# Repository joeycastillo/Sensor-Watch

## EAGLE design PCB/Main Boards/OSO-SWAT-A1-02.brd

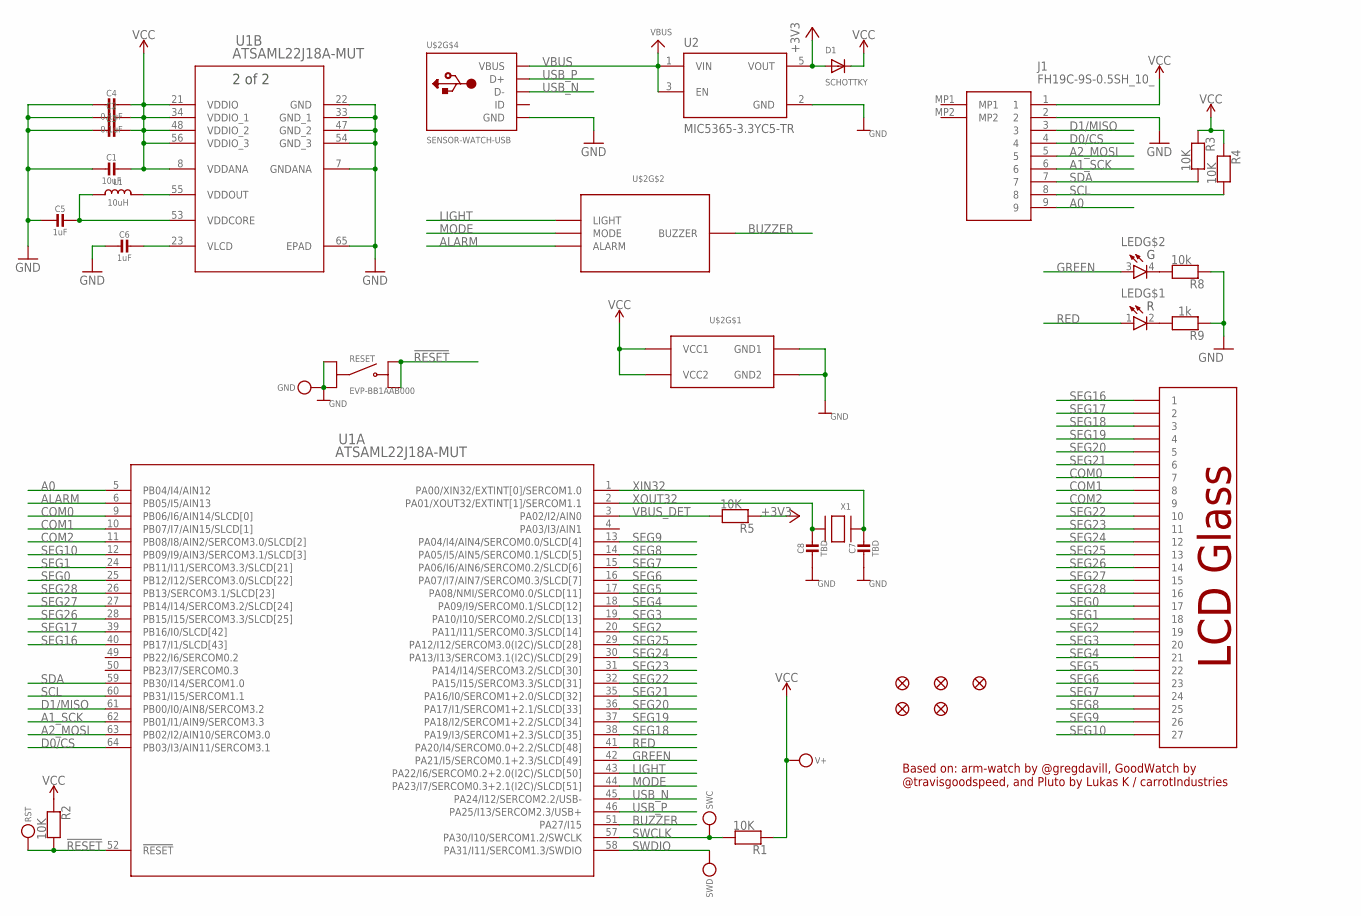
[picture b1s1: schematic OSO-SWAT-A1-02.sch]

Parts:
C1: 10uF; _0603MP
C2, C3, C4: 0.1uF; _0603MP
C5, C6: 1uF; _0603MP
C7, C8: TBD; _0402MP
D1: SCHOTTKY; SOD-323F
FID1, FID2, FID3, FID4, FID6: FIDUCIAL_1MM
GND: MICROBUILDER_TESTPOINTROUND1.5MM; MICROBUILDER_TESTPOINT_ROUND_1.5MM
J1: FH19C-9S-0.5SH_10_; FH19C9S05SH10
L1: 10uH; MICROBUILDER__0805MP
LED: QBLP655R; LED_QBLP655R
R1, R2, R3, R4, R5: 10K; _0603MP
R8: 10k; _0603MP
R9: 1k; _0603MP
RESET: EVP-BB1AAB000; SW_EVP-BB1AAB000
RST: MICROBUILDER_TESTPOINTROUND1.5MM; MICROBUILDER_TESTPOINT_ROUND_1.5MM
SWC: MICROBUILDER_TESTPOINTROUND1.5MM; MICROBUILDER_TESTPOINT_ROUND_1.5MM
SWD: MICROBUILDER_TESTPOINTROUND1.5MM; MICROBUILDER_TESTPOINT_ROUND_1.5MM
U1: ATSAML22J18A-MUT; QFN64_9X9MC_MCH
U2: MIC5365-3.3YC5-TR; SOT65P210X110-5N
U$2: SENSOR-WATCH-USB; CASIO-F91W-OUTLINE-USB
V+: MICROBUILDER_TESTPOINTROUND1.5MM; MICROBUILDER_TESTPOINT_ROUND_1.5MM
X1: XTAL-3.2X1.5; XTAL3215

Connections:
!RESET: R2.2, RESET.B1, RESET.B2, RST.P$1, U1.52 (!RESET)
+3V3: D1.A, R5.1, U2.5 (VOUT)
A0: J1.9, U1.5 (PB04/I4/AIN12)
A1_SCK: J1.6, U1.62 (PB01/I1/AIN9/SERCOM3.3)
A2_MOSI: J1.5, U1.63 (PB02/I2/AIN10/SERCOM3.0)
ALARM: U1.6 (PB05/I5/AIN13), U$2.ALARM
BUZZER: U1.51 (PA27/I15), U$2.BUZZER
COM0: U1.9 (PB06/I6/AIN14/SLCD[0]), U$2.7
COM1: U1.10 (PB07/I7/AIN15/SLCD[1]), U$2.8
COM2: U1.11 (PB08/I8/AIN2/SERCOM3.0/SLCD[2]), U$2.9
D0/CS: J1.4, U1.64 (PB03/I3/AIN11/SERCOM3.1)
D1/MISO: J1.3, U1.61 (PB00/I0/AIN8/SERCOM3.2)
GND: C1.2, C2.2, C3.2, C4.2, C5.2, C6.2, C7.2, C8.2, GND.P$1, J1.2, R8.1, R9.1, RESET.A1, RESET.A2, U1.7 (GNDANA), U1.22 (GND), U1.33 (GND_1), U1.47 (GND_2), U1.54 (GND_3), U1.65 (EPAD), U2.2 (GND), U$2.GND, U$2.GND1, U$2.GND2
GREEN: LED.3 (A), U1.42 (PA21/I5/SERCOM0.1+2.3/SLCD[49])
LIGHT: U1.43 (PA22/I6/SERCOM0.2+2.0(I2C)/SLCD[50]), U$2.LIGHT
MODE: U1.44 (PA23/I7/SERCOM0.3+2.1(I2C)/SLCD[51]), U$2.MODE
unnamed: LED.4 (C), R8.2
unnamed: LED.2 (C), R9.2
RED: LED.1 (A), U1.41 (PA20/I4/SERCOM0.0+2.2/SLCD[48])
SCL: J1.8, R4.2, U1.60 (PB31/I15/SERCOM1.1)
SDA: J1.7, R3.2, U1.59 (PB30/I14/SERCOM1.0)
SEG0: U1.25 (PB12/I12/SERCOM3.0/SLCD[22]), U$2.17
SEG1: U1.24 (PB11/I11/SERCOM3.3/SLCD[21]), U$2.18
SEG2: U1.20 (PA11/I11/SERCOM0.3/SLCD[14]), U$2.19
SEG3: U1.19 (PA10/I10/SERCOM0.2/SLCD[13]), U$2.20
SEG4: U1.18 (PA09/I9/SERCOM0.1/SLCD[12]), U$2.21
SEG5: U1.17 (PA08/NMI/SERCOM0.0/SLCD[11]), U$2.22
SEG6: U1.16 (PA07/I7/AIN7/SERCOM0.3/SLCD[7]), U$2.23
SEG7: U1.15 (PA06/I6/AIN6/SERCOM0.2/SLCD[6]), U$2.24
SEG8: U1.14 (PA05/I5/AIN5/SERCOM0.1/SLCD[5]), U$2.25
SEG9: U1.13 (PA04/I4/AIN4/SERCOM0.0/SLCD[4]), U$2.26
SEG10: U1.12 (PB09/I9/AIN3/SERCOM3.1/SLCD[3]), U$2.27
SEG16: U1.40 (PB17/I1/SLCD[43]), U$2.1
SEG17: U1.39 (PB16/I0/SLCD[42]), U$2.2
SEG18: U1.38 (PA19/I3/SERCOM1+2.3/SLCD[35]), U$2.3
SEG19: U1.37 (PA18/I2/SERCOM1+2.2/SLCD[34]), U$2.4
SEG20: U1.36 (PA17/I1/SERCOM1+2.1/SLCD[33]), U$2.5
SEG21: U1.35 (PA16/I0/SERCOM1+2.0/SLCD[32]), U$2.6
SEG22: U1.32 (PA15/I15/SERCOM3.3/SLCD[31]), U$2.10
SEG23: U1.31 (PA14/I14/SERCOM3.2/SLCD[30]), U$2.11
SEG24: U1.30 (PA13/I13/SERCOM3.1(I2C)/SLCD[29]), U$2.12
SEG25: U1.29 (PA12/I12/SERCOM3.0(I2C)/SLCD[28]), U$2.13
SEG26: U1.28 (PB15/I15/SERCOM3.3/SLCD[25]), U$2.14
SEG27: U1.27 (PB14/I14/SERCOM3.2/SLCD[24]), U$2.15
SEG28: U1.26 (PB13/SERCOM3.1/SLCD[23]), U$2.16
SWCLK: R1.2, SWC.P$1, U1.57 (PA30/I10/SERCOM1.2/SWCLK)
SWDIO: SWD.P$1, U1.58 (PA31/I11/SERCOM1.3/SWDIO)
USB_N: U1.45 (PA24/I12/SERCOM2.2/USB-), U$2.USB_N (D-)
USB_P: U1.46 (PA25/I13/SERCOM2.3/USB+), U$2.USB_P (D+)
VBUS: U2.1 (VIN), U2.3 (EN), U$2.VBUS
VBUS_DET: R5.2, U1.3 (PA02/I2/AIN0)
VCC: C1.1, C2.1, C3.1, C4.1, D1.C, J1.1, R1.1, R2.1, R3.1, R4.1, U1.8 (VDDANA), U1.21 (VDDIO), U1.34 (VDDIO_1), U1.48 (VDDIO_2), U1.56 (VDDIO_3), U$2.VCC1, U$2.VCC2, V+.P$1
VDDCORE: C5.1, L1.1, U1.53 (VDDCORE)
VDDOUT: L1.2, U1.55 (VDDOUT)
VLCD: C6.1, U1.23 (VLCD)
XIN32: C7.1, U1.1 (PA00/XIN32/EXTINT[0]/SERCOM1.0), X1.P$1
XOUT32: C8.1, U1.2 (PA01/XOUT32/EXTINT[1]/SERCOM1.1), X1.P$2

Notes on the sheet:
Based on: arm-watch by @gregdavill, GoodWatch by @travisgoodspeed, and Pluto by Lukas K / carrotIndustries

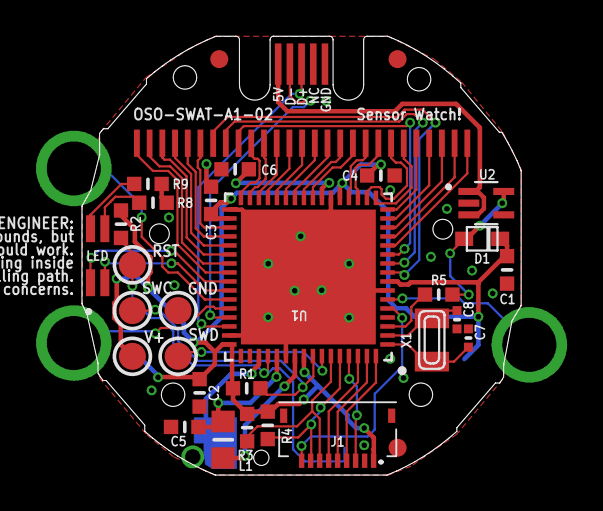
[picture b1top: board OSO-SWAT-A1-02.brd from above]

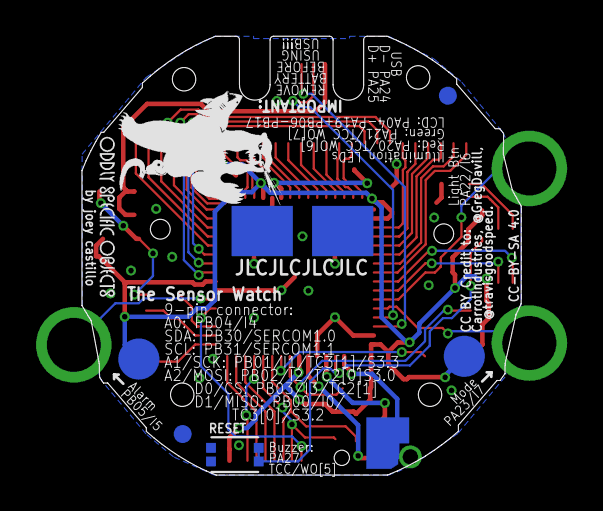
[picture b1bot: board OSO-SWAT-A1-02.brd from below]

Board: 2 copper layers, 24.4 x 24.4 mm, 36 parts (5 on the bottom side), 57 nets.

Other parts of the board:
U$5: OSO_BEAR_250X360MIL_1000DPI
U$6: OSO_WORDMARK_ONELINE_350MIL_1000DPI

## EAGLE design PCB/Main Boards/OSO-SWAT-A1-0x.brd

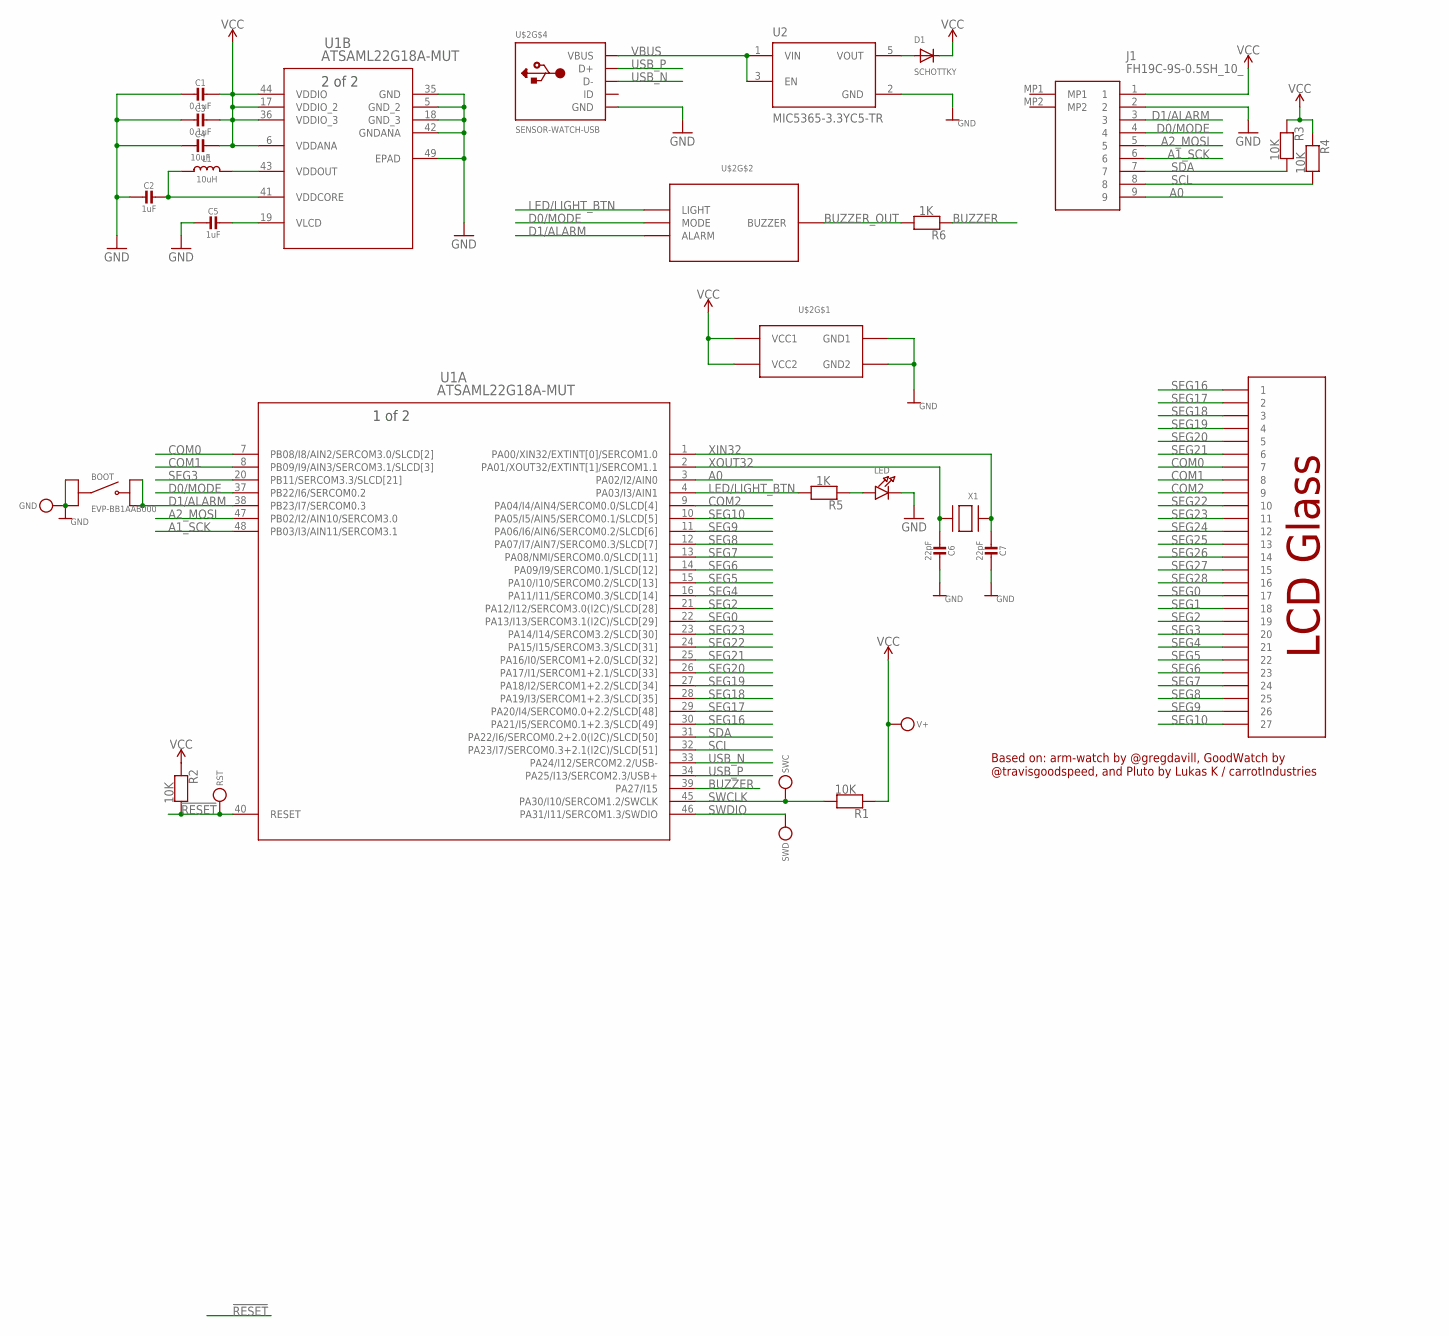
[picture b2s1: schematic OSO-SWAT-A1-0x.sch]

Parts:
BOOT: EVP-BB1AAB000; SW_EVP-BB1AAB000
C1, C3: 0.1uF; _0603MP
C2, C5: 1uF; _0603MP
C4: 10uF; _0603MP
C6, C7: 22pF; _0603MP
D1: SCHOTTKY; SOD-323F
GND: MICROBUILDER_TESTPOINTPAD1MM; MICROBUILDER_TESTPOINT_PAD_1MM
J1: FH19C-9S-0.5SH_10_; FH19C9S05SH10
L1: 10uH; MICROBUILDER__0805MP
LED: LED0805_NOOUTLINE; CHIPLED_0805_NOOUTLINE
R1, R3, R4: 10K; _0603MP
R2: 10K; _0402MP
R5, R6: 1K; _0603MP
RST: MICROBUILDER_TESTPOINTPAD1MM; MICROBUILDER_TESTPOINT_PAD_1MM
SWC: MICROBUILDER_TESTPOINTPAD1MM; MICROBUILDER_TESTPOINT_PAD_1MM
SWD: MICROBUILDER_TESTPOINTPAD1MM; MICROBUILDER_TESTPOINT_PAD_1MM
U1: ATSAML22G18A-MUT; QFN48_7X7MC_MCH
U2: MIC5365-3.3YC5-TR; SOT65P210X110-5N
U$2: SENSOR-WATCH-USB; CASIO-F91W-OUTLINE-USB
V+: MICROBUILDER_TESTPOINTPAD1MM; MICROBUILDER_TESTPOINT_PAD_1MM
X1: XTAL-3.2X1.5; XTAL3215

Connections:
3.3V: D1.A, U2.5 (VOUT)
!RESET: R2.2, RST.P$1, U1.40 (RESET)
A0: J1.9, U1.3 (PA02/I2/AIN0)
A1_SCK: J1.6, U1.48 (PB03/I3/AIN11/SERCOM3.1)
A2_MOSI: J1.5, U1.47 (PB02/I2/AIN10/SERCOM3.0)
BUZZER: R6.1, U1.39 (PA27/I15)
BUZZER_OUT: R6.2, U$2.BUZZER
COM0: U1.7 (PB08/I8/AIN2/SERCOM3.0/SLCD[2]), U$2.7
COM1: U1.8 (PB09/I9/AIN3/SERCOM3.1/SLCD[3]), U$2.8
COM2: U1.9 (PA04/I4/AIN4/SERCOM0.0/SLCD[4]), U$2.9
D0/MODE: J1.4, U1.37 (PB22/I6/SERCOM0.2), U$2.MODE
D1/ALARM: BOOT.B1, BOOT.B2, J1.3, U1.38 (PB23/I7/SERCOM0.3), U$2.ALARM
GND: BOOT.A1, BOOT.A2, C1.2, C2.2, C3.2, C4.2, C5.2, C6.2, C7.2, GND.P$1, J1.2, LED.C, U1.5 (GND_2), U1.18 (GND_3), U1.35 (GND), U1.42 (GNDANA), U1.49 (EPAD), U2.2 (GND), U$2.GND, U$2.GND1, U$2.GND2
LED/LIGHT_BTN: R5.2, U1.4 (PA03/I3/AIN1), U$2.LIGHT
unnamed: LED.A, R5.1
SCL: J1.8, R4.2, U1.32 (PA23/I7/SERCOM0.3+2.1(I2C)/SLCD[51])
SDA: J1.7, R3.2, U1.31 (PA22/I6/SERCOM0.2+2.0(I2C)/SLCD[50])
SEG0: U1.22 (PA13/I13/SERCOM3.1(I2C)/SLCD[29]), U$2.17
SEG1: U$2.18
SEG2: U1.21 (PA12/I12/SERCOM3.0(I2C)/SLCD[28]), U$2.19
SEG3: U1.20 (PB11/SERCOM3.3/SLCD[21]), U$2.20
SEG4: U1.16 (PA11/I11/SERCOM0.3/SLCD[14]), U$2.21
SEG5: U1.15 (PA10/I10/SERCOM0.2/SLCD[13]), U$2.22
SEG6: U1.14 (PA09/I9/SERCOM0.1/SLCD[12]), U$2.23
SEG7: U1.13 (PA08/NMI/SERCOM0.0/SLCD[11]), U$2.24
SEG8: U1.12 (PA07/I7/AIN7/SERCOM0.3/SLCD[7]), U$2.25
SEG9: U1.11 (PA06/I6/AIN6/SERCOM0.2/SLCD[6]), U$2.26
SEG10: U1.10 (PA05/I5/AIN5/SERCOM0.1/SLCD[5]), U$2.27
SEG16: U1.30 (PA21/I5/SERCOM0.1+2.3/SLCD[49]), U$2.1
SEG17: U1.29 (PA20/I4/SERCOM0.0+2.2/SLCD[48]), U$2.2
SEG18: U1.28 (PA19/I3/SERCOM1+2.3/SLCD[35]), U$2.3
SEG19: U1.27 (PA18/I2/SERCOM1+2.2/SLCD[34]), U$2.4
SEG20: U1.26 (PA17/I1/SERCOM1+2.1/SLCD[33]), U$2.5
SEG21: U1.25 (PA16/I0/SERCOM1+2.0/SLCD[32]), U$2.6
SEG22: U1.24 (PA15/I15/SERCOM3.3/SLCD[31]), U$2.10
SEG23: U1.23 (PA14/I14/SERCOM3.2/SLCD[30]), U$2.11
SEG24: U$2.12
SEG25: U$2.13
SEG26: U$2.14
SEG27: U$2.15
SEG28: U$2.16
SWCLK: R1.2, SWC.P$1, U1.45 (PA30/I10/SERCOM1.2/SWCLK)
SWDIO: SWD.P$1, U1.46 (PA31/I11/SERCOM1.3/SWDIO)
USB_N: U1.33 (PA24/I12/SERCOM2.2/USB-), U$2.USB_N (D-)
USB_P: U1.34 (PA25/I13/SERCOM2.3/USB+), U$2.USB_P (D+)
VBUS: U2.1 (VIN), U2.3 (EN), U$2.VBUS
VCC: C1.1, C3.1, C4.1, D1.C, J1.1, R1.1, R2.1, R3.1, R4.1, U1.6 (VDDANA), U1.17 (VDDIO_2), U1.36 (VDDIO_3), U1.44 (VDDIO), U$2.VCC1, U$2.VCC2, V+.P$1
VDDCORE: C2.1, L1.1, U1.41 (VDDCORE)
VDDOUT: L1.2, U1.43 (VDDOUT)
VLCD: C5.1, U1.19 (VLCD)
XIN32: C7.1, U1.1 (PA00/XIN32/EXTINT[0]/SERCOM1.0), X1.P$1
XOUT32: C6.1, U1.2 (PA01/XOUT32/EXTINT[1]/SERCOM1.1), X1.P$2

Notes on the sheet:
Based on: arm-watch by @gregdavill, GoodWatch by @travisgoodspeed, and Pluto by Lukas K / carrotIndustries

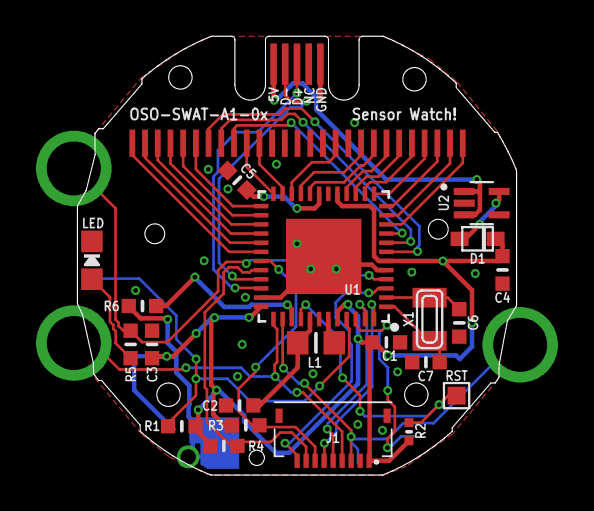
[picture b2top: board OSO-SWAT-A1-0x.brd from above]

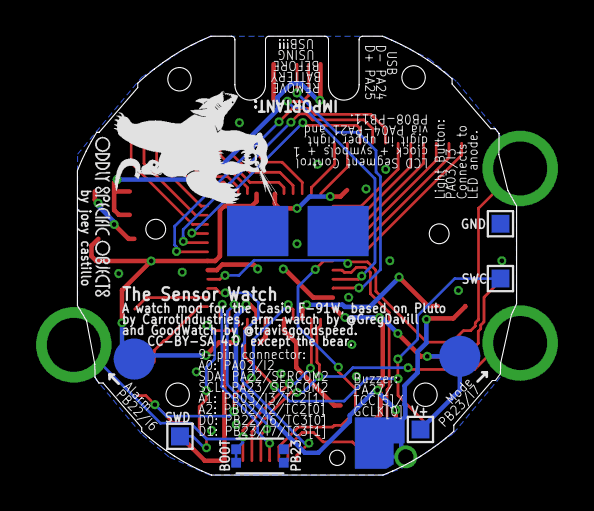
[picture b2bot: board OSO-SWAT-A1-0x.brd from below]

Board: 2 copper layers, 24.4 x 24.4 mm, 29 parts (7 on the bottom side), 46 nets.

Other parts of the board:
U$5: OSO_BEAR_250X360MIL_1000DPI
U$6: OSO_WORDMARK_ONELINE_350MIL_1000DPI

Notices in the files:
PCB/Main Boards/OSO-SWAT-A1-02.brd:
CC BY Credit to:
CarrotIndustries, @GregDavill,
CC-BY-SA 4.0
PCB/Main Boards/OSO-SWAT-A1-0x.brd:
CC-BY-SA 4.0, except the bear.
parts and their libraries:
microbuilder: This work is placed in the public domain, and may be freely used for commercial and non-commercial work with the following conditions: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
COPYRIGHT: Copyright (C) 2018 Accelerated Designs. All rights reserved
